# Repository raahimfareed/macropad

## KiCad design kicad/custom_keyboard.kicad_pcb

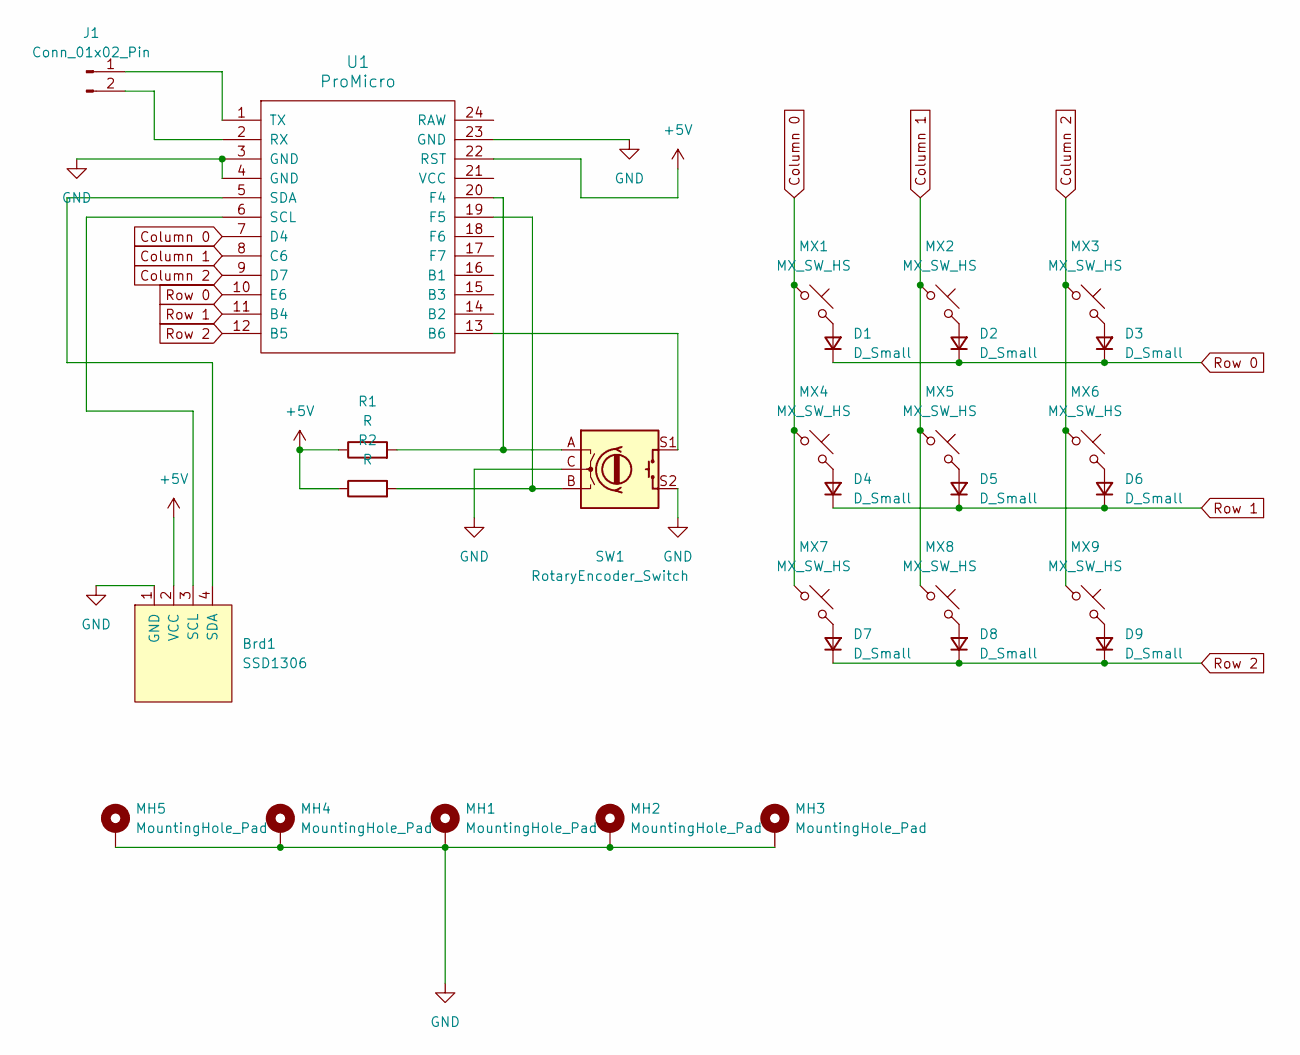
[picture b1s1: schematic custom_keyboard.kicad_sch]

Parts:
Brd1: SSD1306; 128x64OLED
D1, D2, D3, D4, D5, D6, D7, D8, D9: D_Small; D_SOD-123
J1: Conn_01x02_Pin; JST_GH_SM02B-GHS-TB_1x02-1MP_P1.25mm_Horizontal
MH1, MH2, MH3, MH4, MH5: MountingHole_Pad; MountingHole_2.2mm_M2_DIN965_Pad
MX1, MX2, MX3, MX4, MX5, MX6, MX7, MX8, MX9: MX_SW_HS; SW_MX_HS_CPG151101S11_1u
R1, R2: R; R_Axial_DIN0204_L3.6mm_D1.6mm_P5.08mm_Horizontal
SW1: RotaryEncoder_Switch; RotaryEncoder_Alps_EC11E-Switch_Vertical_H20mm
U1: ProMicro; ArduinoProMicro

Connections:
+5V: Brd1.2 (VCC), R1.1, R2.1, U1.22 (RST)
Column 0: MX1.1, MX4.1, MX7.1, U1.7 (D4)
Column 1: MX2.1, MX5.1, MX8.1, U1.8 (C6)
Column 2: MX3.1, MX6.1, MX9.1, U1.9 (D7)
GND: Brd1.1 (GND), MH1.1, MH2.1, MH3.1, MH4.1, MH5.1, SW1.C, SW1.S2, U1.3 (GND), U1.4 (GND), U1.23 (GND)
unnamed: Brd1.3 (SCL), U1.6 (SCL)
unnamed: Brd1.4 (SDA), U1.5 (SDA)
unnamed: D1.2 (A), MX1.2
unnamed: D2.2 (A), MX2.2
unnamed: D3.2 (A), MX3.2
unnamed: D4.2 (A), MX4.2
unnamed: D5.2 (A), MX5.2
unnamed: D6.2 (A), MX6.2
unnamed: D7.2 (A), MX7.2
unnamed: D8.2 (A), MX8.2
unnamed: D9.2 (A), MX9.2
unnamed: J1.1, U1.1 (TX)
unnamed: J1.2, U1.2 (RX)
unnamed: SW1.S1, U1.13 (B6)
unnamed: R1.2, SW1.A, U1.20 (F4)
unnamed: R2.2, SW1.B, U1.19 (F5)
Row 0: D1.1 (K), D2.1 (K), D3.1 (K), U1.10 (E6)
Row 1: D4.1 (K), D5.1 (K), D6.1 (K), U1.11 (B4)
Row 2: D7.1 (K), D8.1 (K), D9.1 (K), U1.12 (B5)

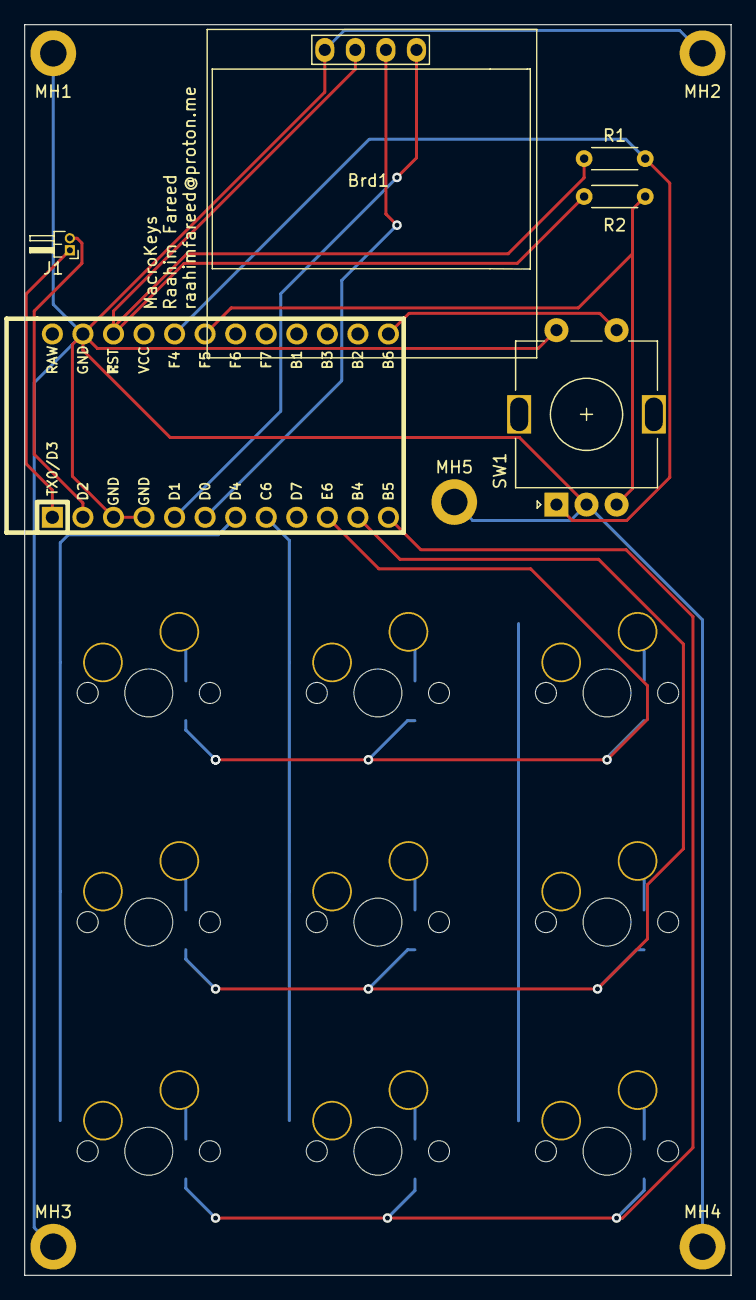
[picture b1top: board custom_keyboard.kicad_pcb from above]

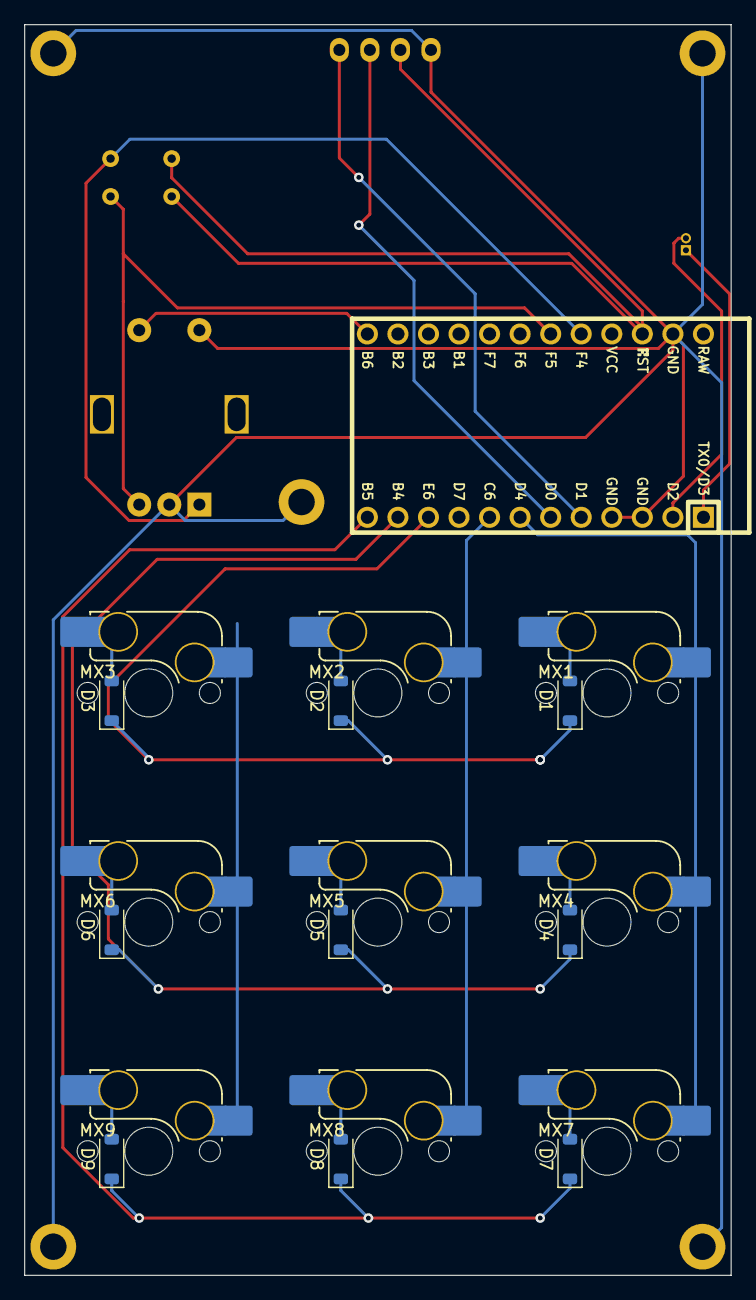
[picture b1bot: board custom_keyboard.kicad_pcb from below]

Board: 2 copper layers, 58.7 x 104.0 mm, 29 parts (18 on the bottom side), 24 nets.

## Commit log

2024-04-28 Init commit
